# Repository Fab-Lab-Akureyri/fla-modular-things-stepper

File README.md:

# fla-modular-things-stepper

## Íslenska
KiCad útgáfa af [RP2040 stepper mótor](https://github.com/modular-things/modular-things/tree/main/arduino/stepper-hbridge-rp2040) [Modular things](https://github.com/modular-things/). 

Byggt á útgáfu [Yuichi Tamiya](https://gitlab.fabcloud.org/yuichitamiya) frá því [Instructors Bootcamp](http://academany.fabcloud.io/fabacademy/2023/instructors-bootcamp/Projects/xiao_rp2040_hbridges/) í [Amsterdam 2023](http://academany.fabcloud.io/fabacademy/2023/instructors-bootcamp/) en með uppfærðum [pinnum](https://github.com/modular-things/modular-things/commit/0fbb3a3acf8de46f2caffaf1a5243ba7b4b4830b). 

## English 

KiCad project [RP2040 stepper motor](https://github.com/modular-things/modular-things/tree/main/arduino/stepper-hbridge-rp2040) [Modular things](https://github.com/modular-things/). 

Based on [Yuichi Tamiya's](https://gitlab.fabcloud.org/yuichitamiya) version from the [Instructors Bootcamp](http://academany.fabcloud.io/fabacademy/2023/instructors-bootcamp/Projects/xiao_rp2040_hbridges/) in [Amsterdam 2023](http://academany.fabcloud.io/fabacademy/2023/instructors-bootcamp/) with updated [pinout](https://github.com/modular-things/modular-things/commit/0fbb3a3acf8de46f2caffaf1a5243ba7b4b4830b). 

## BOM

| NR    | Designator    | Footprint                             | Quantity  | Designation                                   |
| ---   | ---           | ---                                   | ---       | ---                                           |
| 1     |   R6,R7	    | R_1206	                            | 2         | 0 ohm                                         |
| 2     |   M1          | SeeedStudio_XIAO_SocketSMD	        | 1         | XIAO-RP2040_SocketSMD                         |
| 3     |   R2,R4	    | R_2010	                            | 2         | 0.250 ohm                                     |
| 4     |   R3,R1	    | R_1206	                            | 2         | 100 ohm                                       |
| 5     |   C1,C4	    | C_1206	                            | 2         | 0.1 uF                                        |
| 6     |   C5,C2	    | C_1206	                            | 2         | 1uF                                           |
| 7     |   C6,C3	    | C_1206	                            | 2         | 10uF                                          |
| 8     |   UB1,UA1	    | HSOP-8	                            | 2         | TB67H451FNG                                   |
| 9     |   J1	        | PinHeader_1x04_P2.54mm_Horizontal_SMD | 1         | Conn_PinHeader_1x04_P2.54mm_Horizontal_SMD    |

## Images

Note: I only had the male headers for the board, I would have preferred to have the female headers on the board.

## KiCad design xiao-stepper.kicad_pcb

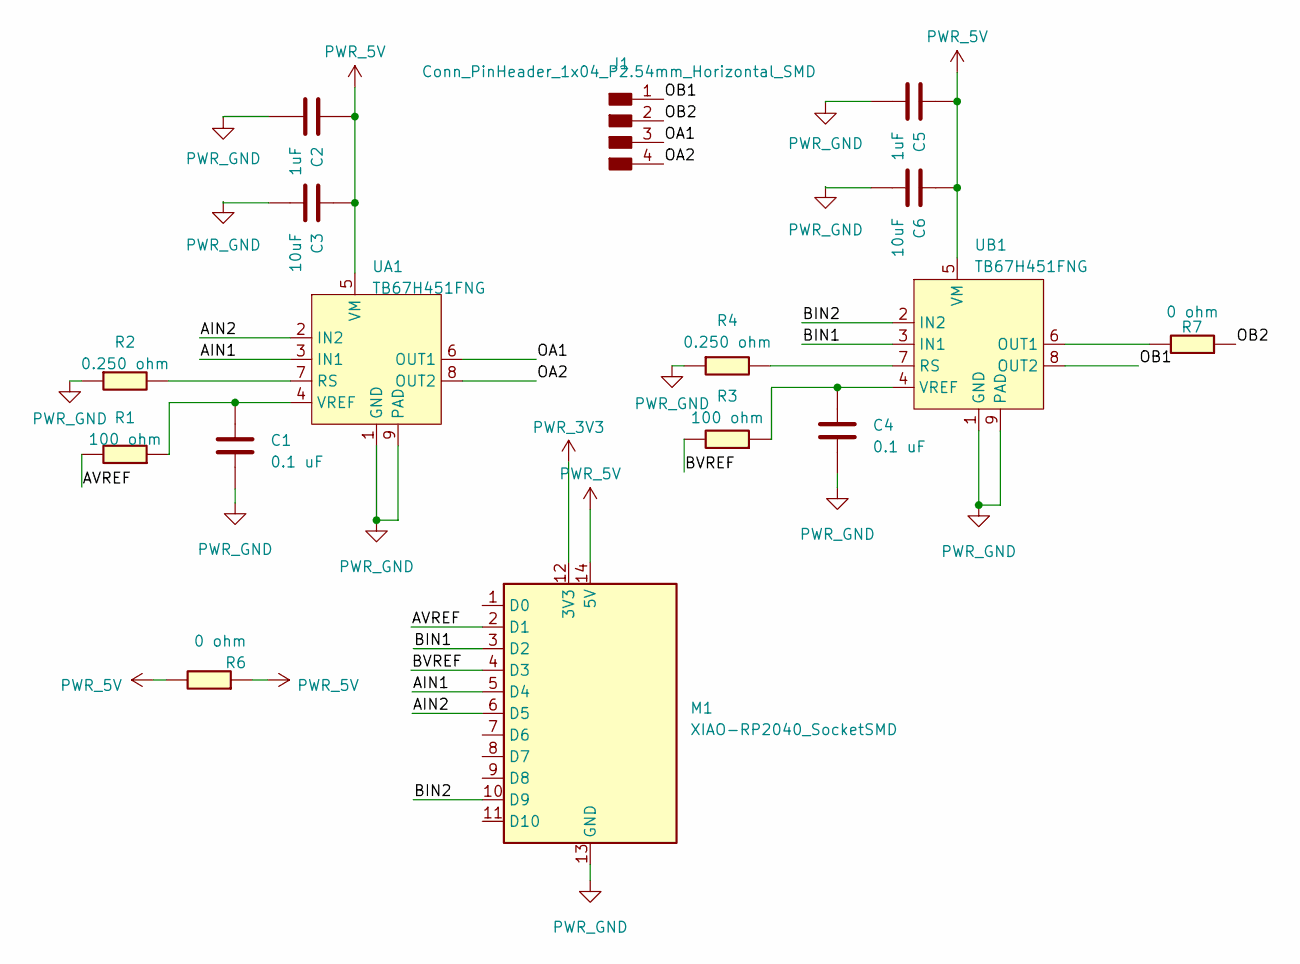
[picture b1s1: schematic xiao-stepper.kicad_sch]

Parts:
C1, C4: 0.1 uF; C_1206
C2, C5: 1uF; C_1206
C3, C6: 10uF; C_1206
J1: Conn_PinHeader_1x04_P2.54mm_Horizontal_SMD; PinHeader_1x04_P2.54mm_Horizontal_SMD
M1: XIAO-RP2040_SocketSMD; SeeedStudio_XIAO_SocketSMD
R1, R3: 100 ohm; R_1206
R2, R4: 0.250 ohm; R_2010
R6, R7: 0 ohm; R_1206
UA1: TB67H451FNG; HSOP-8
UB1: TB67H451FNG; HSOP-8

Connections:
/AIN1: M1.5 (D4), UA1.3 (IN1)
/AIN2: M1.6 (D5), UA1.2 (IN2)
/AVREF: M1.2 (D1), R1.1
/BIN1: M1.3 (D2), UB1.3 (IN1)
/BIN2: M1.10 (D9), UB1.2 (IN2)
/BVREF: M1.4 (D3), R3.1
/OA1: J1.3, UA1.6 (OUT1)
/OA2: J1.4, UA1.8 (OUT2)
/OB1: J1.1, UB1.8 (OUT2)
/OB2: J1.2, R7.2
unnamed: R2.1, UA1.7 (RS)
unnamed: C1.1, R1.2, UA1.4 (VREF)
unnamed: R7.1, UB1.6 (OUT1)
unnamed: R4.1, UB1.7 (RS)
unnamed: C4.1, R3.2, UB1.4 (VREF)
PWR_3V3: M1.12 (3V3)
PWR_5V: C2.1, C3.1, C5.1, C6.1, M1.14 (5V), R6.1, R6.2, UA1.5 (VM), UB1.5 (VM)
PWR_GND: C1.2, C2.2, C3.2, C4.2, C5.2, C6.2, M1.13 (GND), R2.2, R4.2, UA1.1 (GND), UA1.9 (PAD), UB1.1 (GND), UB1.9 (PAD)

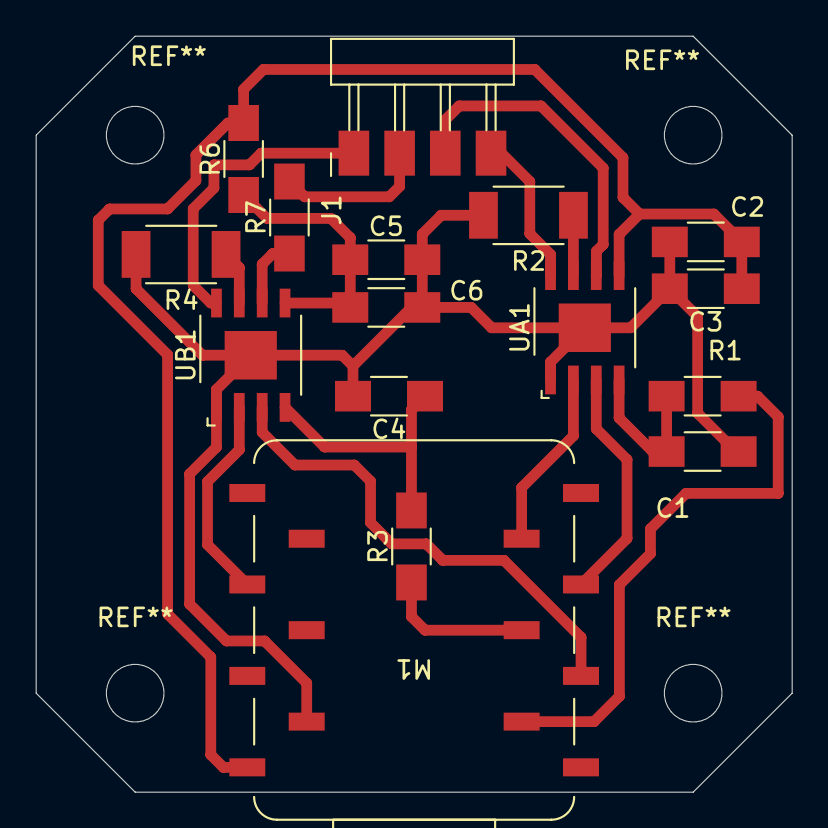
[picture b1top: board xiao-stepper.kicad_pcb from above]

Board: 2 copper layers, 42.0 x 42.0 mm, 16 parts (0 on the bottom side), 17 nets.

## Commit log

2023-05-08 Updated readme and changed 120ohm to 100ohm
2023-05-08 Added images
2023-05-08 Typo
2023-05-08 Updated pcb image
2023-05-08 Updated PCB schematic
